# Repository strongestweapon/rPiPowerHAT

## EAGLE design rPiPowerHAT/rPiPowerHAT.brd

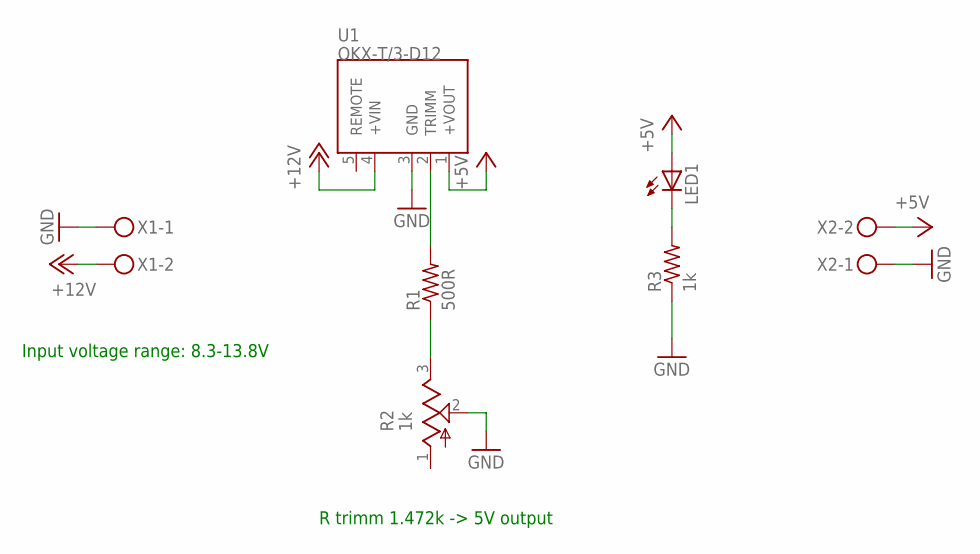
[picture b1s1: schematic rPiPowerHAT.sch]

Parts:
LED1: LEDCHIP-LED0603; CHIP-LED0603
R1: 500R; R0603
R2: 1k; RTRIM3296W
R3: 1k; R0603
U1: OKX-T/3-D12
X1, X2: MKDSN1,5/2-5,08

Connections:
+5V: LED1.A, U1.1 (+VOUT), X2.2
+12V: U1.4 (+VIN), X1.2
GND: R2.2 (S), R3.1, U1.3 (GND), X1.1, X2.1
unnamed: R1.2, U1.2 (TRIMM)
unnamed: R1.1, R2.3 (E)
unnamed: LED1.C, R3.2

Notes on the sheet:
R trimm 1.472k -> 5V output
Input voltage range: 8.3-13.8V

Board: 2 copper layers, 7 parts (0 on the bottom side), 6 nets, no tracks yet.

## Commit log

2021-04-18 first
